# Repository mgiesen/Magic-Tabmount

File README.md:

# Magic Tabmount

Der "Magic Tabmount" ist eine smarte Wandhalterung für das iPad (Generation 5 bis 9). Durch ein integriertes Magnetsystem kann das iPad mit einem Handgriff an der Wand befestigt oder wieder entfernt werden.

Ferner verfügt die Baugruppe über eine integrierte Schaltung, die mittels Radarwellen die Anwesenheit von Personen um das iPad herum detektiert. Werden Personen erkannt, wird das iPad Display aktiviert und bei Abwesenheit deaktiviert.

## Projektmotivation

Insbesondere die älteren iPad Modelle entsprechen heute nur noch selten den Leistungsanforderungen ihrer Nutzer. Aufgrund des geringen Wiederverkaufswerts enden sie entsprechend häufig ungenutzt in der Schublade. Eine Wandmontage ermöglicht verschiedene Anwendungsmöglichkeiten, für die auch eine ältere Hardware noch geeignet ist. Zum Beispiel:

- Smart Home Steuerungszentrale
- Familien Planer
- Musik Steuerungszentrale
- Dashboards für Fitness/ Stromverbrauch etc.
- Ticker und Nachrichten
- und viele mehr...

Ästhetisch war es mir wichtig, das originale Look and Feel des iPads beizubehalten. Um das Gerät scheinbar unsichtbar montieren zu können, wird auf die Geräterückseite ein Magnetring geklebt, der an der iPad Halterung passgenau gehalten wird.

Die automatische Aktivierung des Displays bei Annäherung fühlt sich nicht nur magisch an, sondern spart auch Zeit und erfordert nicht den Einsatz der Hände, was insbesondere beim Kochen nützich ist.

https://github.com/user-attachments/assets/be153968-7474-4deb-8c27-1ca8d5477d2e

## Technische Challange

In erster Linie ist das Projekt eine technische Challange, denn Apple stellt keine Schnittstelle bereit, um den Aktivierungszustand des Displays zu steuern. Für eine gute Nutzbarkeit in geschützem privaten Umfeld war es jedoch wichtig, dass die zuletzt geöffnete App direkt nach Aktivierung des Displays sichtbar wird.

Um auch den notwendigen Zwischenschritt des "Entsperrens" zu umgehen, habe ich mir ein iPad Display Cover näher angesehen. Klappt man dieses zu und wieder auf, wird das iPad bei deaktiviertem Pincode automatisch entsperrt.

Hierzu verfügt das iPad über zwei magnetoresistive Sensoren, die erkennen, dass ein Smart Cover montiert ist und ob dieses auf- oder zugeklappt ist. Mit einer speziellen Folie, lassen sich die im Cover verbauten Magnete sichtbar machen. Die zwei runden Magnete sind für die Sperrung/Entsperrung des Displays erforderlich.

## Integrierte Schaltung

Die Wandhalterung positioniert einen Permanentmagneten an der oberen linken Gerätekante, um die Anwesenheit eines Smart Covers zu simulieren. Ein zweiter Magnet an der unteren Geräteseite sperrt das Display bei Anwesenheit und entsperrt es bei Abwesenheit. Stellt man die automatische Displaysperre des iPads aus, kann der Displayzustand vollständig durch den iPad Halter bestimmt werden.

Der Einsatz eines Elektromagneten an der unteren Geräteseite liegt initial auf der Hand. Jedoch ist der im iPad verbaute Magnetsensor auf der Geräteoberseite verbaut. Daher muss ein besonders starkes Magnetfeld aufgebaut werden, welches geeignet ist den Sensor durch Gehäuse, Akku und Display hindurch zu aktivieren. Der Einsatz eines Elektromagneten würde hier zu einem hohen permaneten Stromverbrauch führen.

Daher habe ich mich dazu entschlossen, einen starken Neodymmagnet einzusetzen, der durch einen kleinen Stepper Motor verschoben wird. Dies führt zu einem minimalen Stromverbrauch, da nur beim Änderung des Displayzustandes Energie benötigt wird.

In Summe integriert die Schaltung entsprechend einen mmWave-Radarsensor, zur Anwesenheitserkennung von Personen, einen kleinen Stepper Motor zur Verschiebung des Magneten, sowie entsprechender Steuerungselektronik.

## Planung der Elektronik

Um den Stromanschluss der Platine mit einer Lademöglichkeit des iPads zu kombinieren, habe ich zwei USB C Anschlüsse auf der Platine verbaut. Der nach unten ausgerichtete Port, ist für ein Stromkabel vorgesehen. Der zweite Port ist auf gleicher Höhe wie der Lightning Anschluss des iPads positioniert. Somit kann ein kurzes Verbindungskabel zwischen iPad und Wandhalterung zum Laden des iPads eingesetzt werden.

Zur Auswertung der Signale und Steuerung der Logik ist ein Mikrocontroller verbaut, der direkt über den Host Port programmiert werden kann. Zur Steuerung des Motors wird zudem ein Stepper Treiber benötigt. Der Umfang der Elektronik und entsprechender Komplexität erfordert ein Custom-PCB Design, welches ich mit KiCad umgesetzt habe.

Für eine besondere, persönliche Note, habe ich das vorderseitige Produktlogo aus Semi-Transparentem Material gedruckt, um es aktiv zu hinterleuchten. Somit integriert die Platine zusätzlich vier RGB LEDs, die über den Mikrocontroller gesteuert werden. Ein rückseitig verbauter Hall-Sensor prüft, ob das iPad anliegt, oder nicht. Sobald das iPad angelegt ist, wird die Logobeleuchtung ausgeschlatet.

### PCB Layout

Aufgrund der hohen Anzahl an Elektronik Komponenten, habe ich versucht ausschließlich auf SMD Komponenten zu setzen, sodass ich einen Großteil der Komponetnten mittels Stencil bestücken konnte. Funktionsbedingt musste lediglich der Hall Sensor zur Geräteerkennung, als auch die Logobeleuchtung auf die Unterseite des PCBs gelegt werden.

### Ergebnis

Mittels Stencil und Hot-Plate ließen sich alle Komponenten schnell und einfach verlöten. Das PCB wird mit vier Schrauben im Gehäuse befestigt und der Stepper Motor am Platinenrand verlötet. Für die Zukunft wäre ein Stecker praktikabeler, jedoch war diese Lösung kurzfristig am kostengünstigsten.

Die seitliche Tasche ermöglicht es ein Standard USB C auf Lightning Kabel einzurollen und das Gerät über einen Winkeladapter zu laden.

## Gehäuse

Während des Prototypings und ohne sonderlichen Fokus auf einen marketingtauglichen Namen, lief der Wandhalter unter dem Projektnamen "Magic iPad Wallmount". Um keine Markenrechte zu verletzten, änderte ich den Namen zum Projektende auf Magic Tabmount.

Das Gehäusedesign sollte initial kleinstmöglich und funktionsorientiert gestaltet sein.

Problemtaisch war der Magnet an der oberen Geräteecke, ohne den eine Steuerung des Displays nicht möglich war. Der zuerst aufgeklebte Magnet störte bei der Bedienung des Tablets in der Hand, weswegen ich das Design an die Gerätemaße anglich, um den Magnet zu integrieren.

Hinter einer kraftschlüssig aufgesetzten Kappe, liegen zwei Schraubpunkte, über die der Halter an der Wand montiert werden kann.

Für eine gute Druckbarkeit des Gehäuses und einheitliche Oberflächen, mussten alle Oberseiten auf der Druckplatte des 3D Druckers aufliegen.

Daher ist der innere Ring mehrteilig gedruckt und anschließend formschlüssig montiert und verschraubt.

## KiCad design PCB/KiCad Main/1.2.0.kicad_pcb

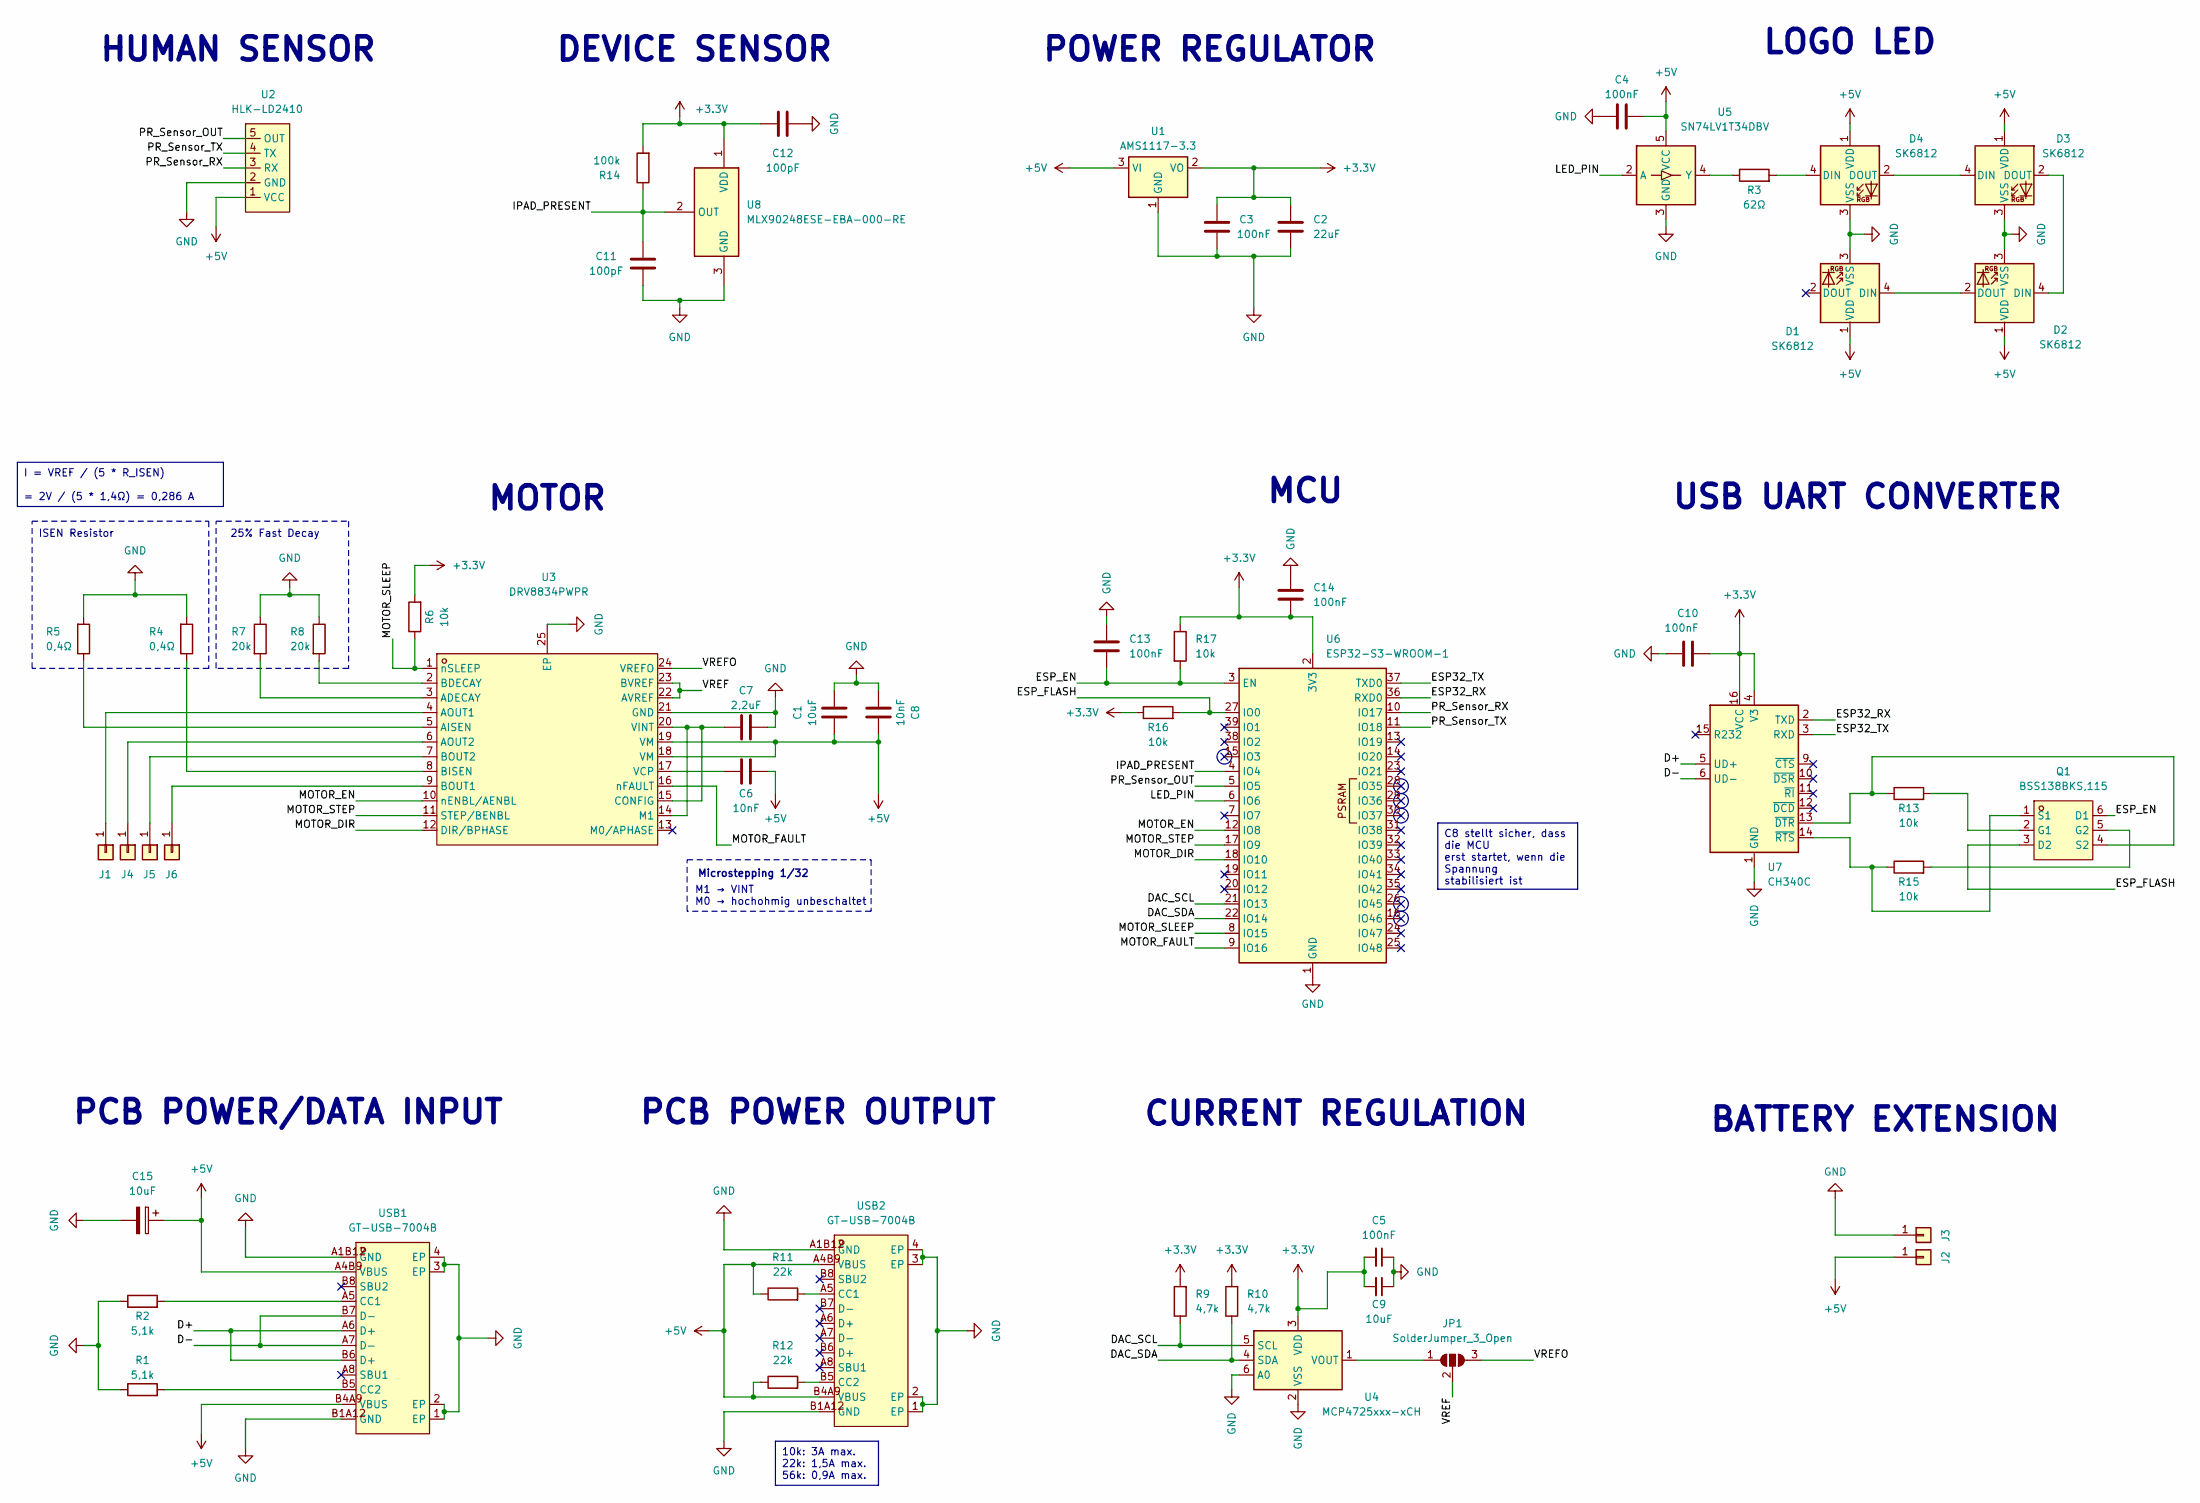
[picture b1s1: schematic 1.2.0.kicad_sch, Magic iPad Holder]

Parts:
C1: 10uF; C_1206_3216Metric; LCSC Part C13585
C2: 22uF; C_1206_3216Metric; LCSC Part C12891
C3, C10, C13, C14: 100nF; C_1206_3216Metric; LCSC Part C82601
C4: 100nF; C_1206_3216Metric; LCSC Part C107186
C5: 100nF; C_1206_3216Metric
C6, C8: 10nF; C_1206_3216Metric; LCSC Part C77498
C7: 2,2uF; C_1206_3216Metric; LCSC Part C107186
C9: 10uF; C_1206_3216Metric
C11, C12: 100pF; C_1206_3216Metric; LCSC Part C113876
C15: 10uF; CP_Elec_5x3; LCSC Part C340737
D1, D2, D3, D4: SK6812; LED_WS2812B_PLCC4_5.0x5.0mm_P3.2mm; LCSC Part C5380881
J1, J2, J3, J4, J5, J6: Solder Pad; TestPoint_Pad_1.5x1.5mm
JP1: SolderJumper_3_Open; SolderJumper-3_P1.3mm_Open_RoundedPad1.0x1.5mm
Q1: BSS138BKS,115; SOT-363_L2.0-W1.3-P0.65-LS2.1-BR; LCSC Part C456075
R1, R2: 5,1k; R_1206_3216Metric; LCSC Part C163372
R3: 62Ω; R_1206_3216Metric; LCSC Part C17902
R4, R5: 0,4Ω; R_1206_3216Metric; LCSC Part C5126044
R6, R13, R15, R16, R17: 10k; R_1206_3216Metric; LCSC Part C17902
R7, R8: 20k; R_1206_3216Metric; LCSC Part C18003
R9, R10: 4,7k; R_1206_3216Metric; LCSC Part C25830
R11, R12: 22k; R_1206_3216Metric; LCSC Part C25830
R14: 100k; R_1206_3216Metric; LCSC Part C17900
U1: AMS1117-3.3; SOT-223-3_TabPin2; Mouser Part Number 926-LM1117MPX3.3NOPB; LCSC Part C347222
U2: HLK-LD2410; HDR-SMD_5P-P2.54-H-F_X6511FRS-19-C85D30; LCSC Part C5183133
U3: DRV8834PWPR; HTSSOP-24_L7.8-W4.4-P0.65-BL-EP; Mouser Part Number 595-DRV8834PWP; LCSC Part C456273
U4: MCP4725xxx-xCH; SOT-23-6
U5: SN74LV1T34DBV; SOT-23-5
U6: ESP32-S3-WROOM-1; Mouser Part Number 356-ESP32-S3WROOM1N8; LCSC Part C2913198
U7: CH340C; SOIC-16_3.9x9.9mm_P1.27mm; LCSC Part C84681
U8: MLX90248ESE-EBA-000-RE; SOT95P280X100-3N; Mouser Part Number 482-90248ESEEBA000RE
USB1, USB2: GT-USB-7004B; USB-C-SMD_GT-USB-7004B; LCSC Part C5368946

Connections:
+3.3V: C2.1, C3.2, C5.2, C9.2, C10.1, C12.2, C14.1, R6.2, R9.2, R10.2, R14.2, R16.1, R17.1, U1.2 (VO), U4.3 (VDD), U6.2 (3V3), U7.4 (V3), U7.16 (VCC), U8.1 (VDD)
+5V: C1.1, C4.2, C6.2, C8.2, C15.1, D1.1 (VDD), D2.1 (VDD), D3.1 (VDD), D4.1 (VDD), J2.1, R11.1, R12.1, U1.3 (VI), U2.1 (VCC), U3.18 (VM), U3.19 (VM), U5.5 (VCC), USB1.A4B9 (VBUS), USB1.B4A9 (VBUS), USB2.A4B9 (VBUS), USB2.B4A9 (VBUS)
/D+: U7.5 (UD+), USB1.A6 (D+), USB1.B6 (D+)
/D-: U7.6 (UD-), USB1.A7 (D-), USB1.B7 (D-)
/DAC_SCL: R9.1, U4.5 (SCL), U6.21 (IO13)
/DAC_SDA: R10.1, U4.4 (SDA), U6.22 (IO14)
/ESP32_RX: U6.36 (RXD0), U7.2 (TXD)
/ESP32_TX: U6.37 (TXD0), U7.3 (RXD)
/ESP_EN: C13.1, Q1.6 (D1), R17.2, U6.3 (EN)
/ESP_FLASH: Q1.3 (D2), R16.2, U6.27 (IO0)
/IPAD_PRESENT: C11.2, R14.1, U6.4 (IO4), U8.2 (OUT)
/LED_PIN: U5.2 (A), U6.6 (IO6)
/MOTOR_DIR: U3.12 (DIR/BPHASE), U6.18 (IO10)
/MOTOR_EN: U3.10 (nENBL/AENBL), U6.12 (IO8)
/MOTOR_FAULT: U3.16 (nFAULT), U6.9 (IO16)
/MOTOR_SLEEP: R6.1, U3.1 (nSLEEP), U6.8 (IO15)
/MOTOR_STEP: U3.11 (STEP/BENBL), U6.17 (IO9)
/PR_Sensor_OUT: U2.5 (OUT), U6.5 (IO5)
/PR_Sensor_RX: U2.3 (RX), U6.10 (IO17)
/PR_Sensor_TX: U2.4 (TX), U6.11 (IO18)
/VREF: JP1.2 (C), U3.22 (AVREF), U3.23 (BVREF)
/VREFO: JP1.3 (B), U3.24 (VREFO)
GND: C1.2, C2.2, C3.1, C4.1, C5.1, C7.2, C8.1, C9.1, C10.2, C11.1, C12.1, C13.2, C14.2, C15.2, D1.3 (VSS), D2.3 (VSS), D3.3 (VSS), D4.3 (VSS), J3.1, R1.1, R2.1, R4.2, R5.2, R7.1, R8.1, U1.1 (GND), U2.2 (GND), U3.21 (GND), U3.25 (EP), U4.2 (VSS), U4.6 (A0), U5.3 (GND), U6.1 (GND), U6.40 (GND), U6.41 (GND), U7.1 (GND), U8.3 (GND), USB1.1 (EP), USB1.2 (EP), USB1.3 (EP), USB1.4 (EP), USB1.A1B12 (GND), USB1.B1A12 (GND), USB2.1 (EP), USB2.2 (EP), USB2.3 (EP), USB2.4 (EP), USB2.A1B12 (GND), USB2.B1A12 (GND)
unnamed: D1.4 (DIN), D2.2 (DOUT)
unnamed: D2.4 (DIN), D3.2 (DOUT)
unnamed: D3.4 (DIN), D4.2 (DOUT)
unnamed: D4.4 (DIN), R3.2
unnamed: J1.1, U3.4 (AOUT1)
unnamed: J4.1, U3.6 (AOUT2)
unnamed: J5.1, U3.7 (BOUT2)
unnamed: J6.1, U3.9 (BOUT1)
unnamed: JP1.1 (A), U4.1 (VOUT)
unnamed: Q1.2 (G1), R13.2
unnamed: Q1.5 (G2), R15.2
unnamed: Q1.1 (S1), R15.1, U7.14 (~RTS)
unnamed: Q1.4 (S2), R13.1, U7.13 (~DTR)
unnamed: R7.2, U3.3 (ADECAY)
unnamed: R5.1, U3.5 (AISEN)
unnamed: R8.2, U3.2 (BDECAY)
unnamed: R4.1, U3.8 (BISEN)
unnamed: C7.1, U3.14 (M1), U3.15 (CONFIG), U3.20 (VINT)
unnamed: C6.1, U3.17 (VCP)
unnamed: R3.1, U5.4 (Y)
unnamed: R2.2, USB1.A5 (CC1)
unnamed: R1.2, USB1.B5 (CC2)
unnamed: R11.2, USB2.A5 (CC1)
unnamed: R12.2, USB2.B5 (CC2)

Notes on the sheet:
C8 stellt sicher, dass die MCU erst startet, wenn die Spannung stabilisiert ist
10k: 3A max. 22k: 1,5A max. 56k: 0,9A max.
I = VREF / (5 * R_ISEN) = 2V / (5 * 1,4Ω) = 0,286 A
Microstepping 1/32
CURRENT REGULATION
MCU
MOTOR
PCB POWER OUTPUT
PCB POWER/DATA INPUT
HUMAN SENSOR
USB UART CONVERTER
LOGO LED
M1 → VINT M0 → hochohmig unbeschaltet
BATTERY EXTENSION
POWER REGULATOR
25% Fast Decay
DEVICE SENSOR
ISEN Resistor

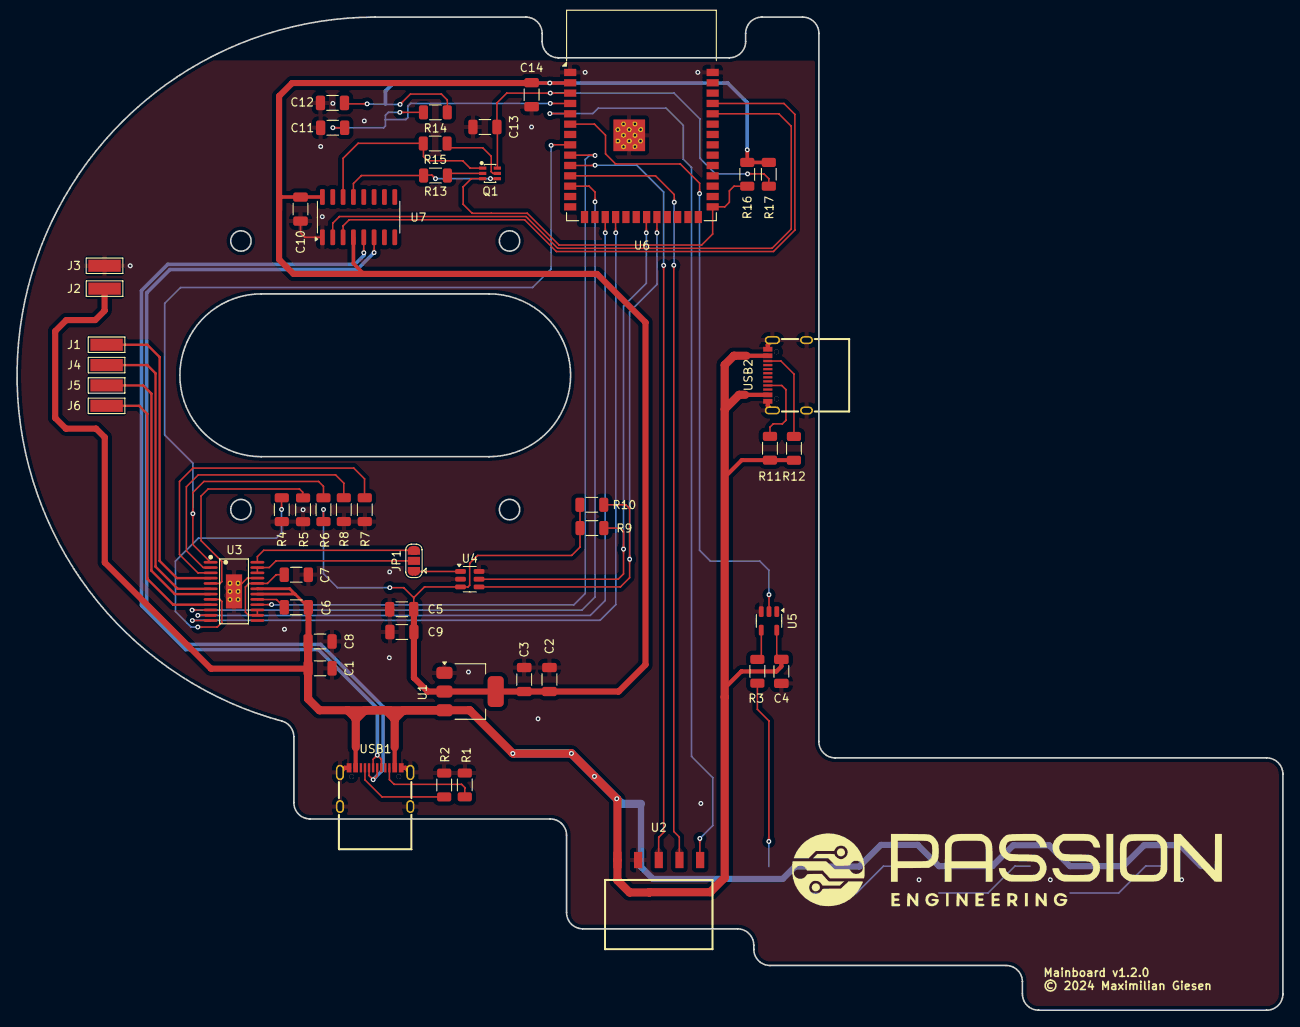
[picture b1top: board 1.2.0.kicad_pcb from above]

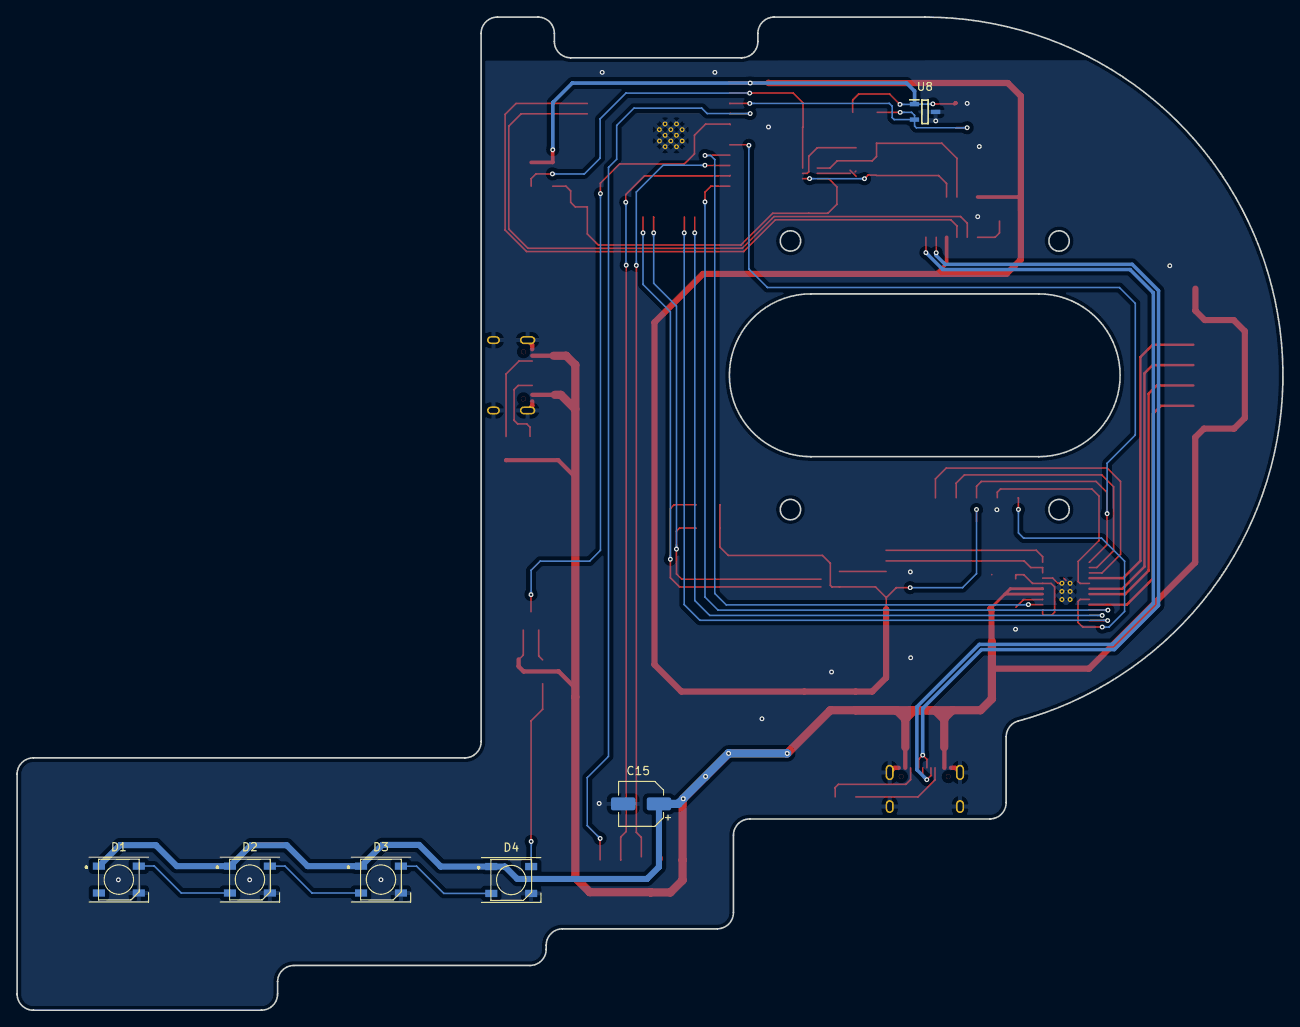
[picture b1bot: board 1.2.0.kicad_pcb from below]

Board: 2 copper layers, 155.5 x 122.0 mm, 54 parts (6 on the bottom side), 47 nets.

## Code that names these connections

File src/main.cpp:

// ************************************************************************
// Includes und Definitionen
// ************************************************************************

// Kern-Bibliotheken für Arduino & ESP32
#include <Arduino.h>
#include <WiFi.h>
#include <SPIFFS.h>
#include <Wire.h>

// Kommunikationsbibliotheken
#include <AsyncTCP.h>
#include <ESPAsyncWebServer.h>
#include <Adafruit_MCP4725.h>
#include <ArduinoJson.h>
#include <WiFiUdp.h>

// Benutzerdefinierte Hardware-Bibliotheken
#include "LogoLED.h"
#include "DeviceDetection.h"
#include "DisplayController.h"
#include "LD2410.h"
#include "FirmwareUpdate.h"

// ************************************************************************
// Pin und Konstanten Definitionen
// ************************************************************************

// Namensgebung
#define DEBUG_SERIAL Serial
#define RADAR_SERIAL Serial2

// Logo LED
#define NUMBER_OF_LEDS 4
#define LED_PIN 6

// Geräteerkennung
#define DEVICE_SENSOR_PIN 4

// LD2410 Sensor zur Anwesenheitserkennung
#define HUMAN_PRESENCE_PIN 5
#define HUMAN_PRESENCE_RX 17
#define HUMAN_PRESENCE_TX 18

// Schrittmotor
#define STEP_PIN 9
#define DIR_PIN 10
#define STEPPER_ENABLE 8
#define STEPPER_SLEEP 15

#define DAC_I2C_ADDRESS 0x60
#define DAC_SDA_PIN 14
#define DAC_SCL_PIN 13

// ************************************************************************
// Globale Variablen und Instanzen
// ************************************************************************

// Konfiguration des DAC
Adafruit_MCP4725 dac;
TwoWire I2C = TwoWire(0);

// Konfiguration des Webservers
IPAddress apIP(192, 168, 4, 1);
const char *ssid = "Magic Tabmount DEV";
const char *password = "12345678";

// Webserver- und WebSocket-Instanzen
AsyncWebServer server(80);
AsyncWebSocket ws("/ws");

// Vorwärtsdeklarationen
void onHumanPresenceChange(bool presence);
void onDevicePresenceChange(bool presence);
void handleWebSocketMessage(void *arg, uint8_t *data, size_t len);
void onEvent(AsyncWebSocket *server, AsyncWebSocketClient *client, AwsEventType type, void *arg, uint8_t *data, size_t len);

// Laufzeitvariablen
volatile bool humanPresent = false;
volatile bool devicePresent = false;
volatile bool stateChange = true;

// Instanzen
HardwareSerial SensorSerial(1);
LD2410 humanSensor;
LogoLED<LED_PIN> logoLED(NUMBER_OF_LEDS);
DeviceDetection deviceSensor(DEVICE_SENSOR_PIN, INPUT_PULLUP, devicePresent);
DisplayController displayController(STEP_PIN, DIR_PIN, STEPPER_ENABLE, STEPPER_SLEEP, 10, 3500, 700);
FirmwareUpdateManager *firmwareUpdateManager;

// Logo Helligkeit
int logoBrightness = 230;

// Warteschlange für Statusänderungen
struct StateUpdate
{
  bool human;
  bool device;
  bool valid;
} stateQueue;

portMUX_TYPE stateMux = portMUX_INITIALIZER_UNLOCKED;

// Timer für verzögerte Aktualisierungen
hw_timer_t *updateTimer = NULL;
volatile bool updatePending = false;

// ************************************************************************
// Interrupt Service Routinen
// ************************************************************************

void IRAM_ATTR onUpdateTimer()
{
  updatePending = true;
}

void IRAM_ATTR onHumanPresenceChange(bool presence)
{
  portENTER_CRITICAL_ISR(&stateMux);
  humanPresent = presence;
  stateQueue.human = presence;
  stateQueue.valid = true;
  stateChange = true;
  portEXIT_CRITICAL_ISR(&stateMux);
}

void IRAM_ATTR onDevicePresenceChange(bool presence)
{
  portENTER_CRITICAL_ISR(&stateMux);
  devicePresent = presence;
  stateQueue.device = presence;
  stateQueue.valid = true;
  stateChange = true;
  portEXIT_CRITICAL_ISR(&stateMux);
}

// ************************************************************************
// WebSocket Funktionen
// ************************************************************************

void notifyClients()
{
  if (ws.count() > 0)
  { // Nur senden, wenn Clients verbunden sind
    StaticJsonDocument<200> doc;
    doc["humanPresent"] = humanPresent;
    doc["devicePresent"] = devicePresent;
    doc["logoBrightness"] = logoBrightness;

    String jsonString;
    serializeJson(doc, jsonString);

    ws.textAll(jsonString);
  }
}

void handleWebSocketMessage(void *arg, uint8_t *data, size_t len)
{
  AwsFrameInfo *info = (AwsFrameInfo *)arg;
  if (info->final && info->index == 0 && info->len == len && info->opcode == WS_TEXT)
  {
    String message = String((char *)data).substring(0, len);

    if (message.startsWith("setBrightness:"))
    {
      logoBrightness = message.substring(14).toInt();
      logoLED.setBrightness(logoBrightness);
      notifyClients();
    }
  }
}

void onEvent(AsyncWebSocket *server, AsyncWebSocketClient *client, AwsEventType type, void *arg, uint8_t *data, size_t len)
{
  switch (type)
  {
  case WS_EVT_CONNECT:
    // DEBUG_SERIAL.printf("WebSocket-Client #%u verbunden von %s\n", client->id(), client->remoteIP().toString().c_str());
    notifyClients();
    break;
  case WS_EVT_DISCONNECT:
    // DEBUG_SERIAL.printf("WebSocket-Client #%u getrennt\n", client->id());
    break;
  case WS_EVT_DATA:
    handleWebSocketMessage(arg, data, len);
    break;
  case WS_EVT_PONG:
  case WS_EVT_ERROR:
    break;
  }
}

// ************************************************************************
// Initialisierungsfunktionen
// ************************************************************************

void initializeLED()
{
  logoLED.begin();
  logoLED.setBrightness(logoBrightness);
  logoLED.setColor(255, 255, 255);
  logoLED.on();
}

void initializeMotorControl()
{
  pinMode(STEPPER_SLEEP, OUTPUT);
  digitalWrite(STEPPER_SLEEP, HIGH);

  pinMode(STEPPER_ENABLE, OUTPUT);
  digitalWrite(STEPPER_ENABLE, HIGH);

  I2C.begin(DAC_SDA_PIN, DAC_SCL_PIN);
  if (!dac.begin(DAC_I2C_ADDRESS, &I2C))
  {
    // DEBUG_SERIAL.println("MCP4725 nicht gefunden!");
  }
  dac.setVoltage(1350, false);
}

void initializeFileSystem()
{
  if (!SPIFFS.begin(true))
  {
    // DEBUG_SERIAL.println("SPIFFS Fehler beim Mounten");
  }
}

void initializeWiFi()
{
  WiFi.mode(WIFI_AP);
  WiFi.softAP(ssid, password);
  WiFi.softAPConfig(apIP, apIP, IPAddress(255, 255, 255, 0));

  // DEBUG_SERIAL.print("AP IP Adresse: ");
  // DEBUG_SERIAL.println(WiFi.softAPIP());
}

void initializeWebServer()
{
  ws.onEvent(onEvent);
  server.addHandler(&ws);

  server.on("/", HTTP_GET, [](AsyncWebServerRequest *request)
            { request->send(SPIFFS, "/index.html", "text/html"); });

  server.begin();
  // DEBUG_SERIAL.println("HTTP Server gestartet");
}

void initializeTimer()
{
  updateTimer = timerBegin(0, 80, true);
  timerAttachInterrupt(updateTimer, &onUpdateTimer, true);
  timerAlarmWrite(updateTimer, 100000, true);
  timerAlarmEnable(updateTimer);
}

void initializeSensors()
{
  deviceSensor.beginOutputObservation(onDevicePresenceChange);

  // humanSensor.beginUART(HUMAN_PRESENCE_TX, HUMAN_PRESENCE_RX, RADAR_SERIAL); // Weiterleitung der seriellen Kommunikation an USB Port
  SensorSerial.begin(256000, SERIAL_8N1, HUMAN_PRESENCE_TX, HUMAN_PRESENCE_RX);

  humanSensor.beginOutputObservation(HUMAN_PRESENCE_PIN, onHumanPresenceChange, INPUT_PULLDOWN);

  stateQueue.valid = false;
}

void initializeSerial()
{
  delay(10);
  DEBUG_SERIAL.begin(256000);
  delay(100);
}

// ************************************************************************
// Hauptfunktionen für den Loop
// ************************************************************************

void handleStateUpdates()
{
  if (updatePending)
  {
    portENTER_CRITICAL(&stateMux);
    bool shouldUpdate = stateQueue.valid;
    if (shouldUpdate)
    {
      stateQueue.valid = false;
    }
    portEXIT_CRITICAL(&stateMux);

    if (shouldUpdate)
    {
      notifyClients();
    }
    updatePending = false;
  }
}

void updateDeviceState()
{
  if (stateChange)
  {
    if (devicePresent == false)
    {
      if (humanPresent)
      {
        logoLED.setColor(0, 128, 0);
      }
      else
      {
        logoLED.setColor(255, 255, 255);
      }
    }
    else
    {
      logoLED.setColor(0, 0, 0);

      if (humanPresent)
      {
        displayController.activate(true);
      }
      else
      {
        displayController.activate(false);
      }
    }
    stateChange = false;
  }
}

// ************************************************************************
// Arduino Hauptfunktionen
// ************************************************************************

void setup()
{
  initializeSerial();
  initializeLED();
  initializeMotorControl();
  initializeFileSystem();
  initializeWiFi();
  initializeWebServer();
  initializeTimer();
  initializeSensors();
}

void loop()
{
  if (SensorSerial.available())
  {
    DEBUG_SERIAL.write(SensorSerial.read());
  }

  if (DEBUG_SERIAL.available())
  {
    SensorSerial.write(DEBUG_SERIAL.read());
  }

  ws.cleanupClients();
  handleStateUpdates();
  updateDeviceState();
}

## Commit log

2024-11-16 Exclude .vscode
2024-11-16 Ignore DS_Store
2024-11-16 Add LD2410 sensor library as submodule
2024-11-16 Ändere Standardumgebung von 'ota' zu 'usb-fast' und passe Umgebungsnamen an
2024-11-17 Frontend Mockup implementiert
2024-11-17 Design Änderungen an Settings Webapp
2024-11-17 Optimierung der Animation des Dashboards
2024-12-27 Kommunikation LD2410 über USB Port
2024-12-27 Restruktur Repo
2024-12-31 Neuer Dokumentationsstand
2024-12-31 Integration Anwendungsvideo
2026-04-11 Komprimierung der Bilder
2026-06-26 Initial Upload
2026-06-27 Presence-Sensor-Konfiguration und Dashboard-Überarbeitung
    Dashboard:
    - Presence-Sensor-Block zeigt jetzt den Verbindungsstatus (Verbunden/Offline);
    Firmware-Version in eine eigene Detailseite verschoben (Zahnrad-Icon öffnet
    die Ansicht, Zurück-Button führt zurück)
    - Neue Detailseite zum Einstellen der LD2410-Empfindlichkeit pro Gate ("Bänder"):
    je Band zwei Kanäle (Dyn./Stat.) mit Live-Energie-Balken und einstellbarer
2026-06-27 Firmware-README korrigieren und secrets-Altlasten entfernen
    - Firmware/README: falsche Submodule-Anweisung ersetzt durch reale
    PlatformIO-Setup-, Flash- und Konfigurationsschritte (kein Submodule-Schritt,
    lib_deps werden automatisch geladen, zwei Upload-Ziele, dauerhafter AP)
    - secrets.example.h entfernt und src/secrets.h aus .gitignore genommen:
    der AP-only-Rewrite nutzt keine WLAN-STA-Zugangsdaten mehr

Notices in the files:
PCB/KiCad Main/1.2.0.kicad_pcb:
© 2024 Maximilian Giesen
